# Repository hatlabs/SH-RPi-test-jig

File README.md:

# SH-RPi Test Jig software

This repository contains two separate PlatformIO projects, one Raspberry Pi software project, and KiCad hardware design that can be used to implement [SH-RPi](hatlabs.github.io/sh-rpi/) test jig functionality.

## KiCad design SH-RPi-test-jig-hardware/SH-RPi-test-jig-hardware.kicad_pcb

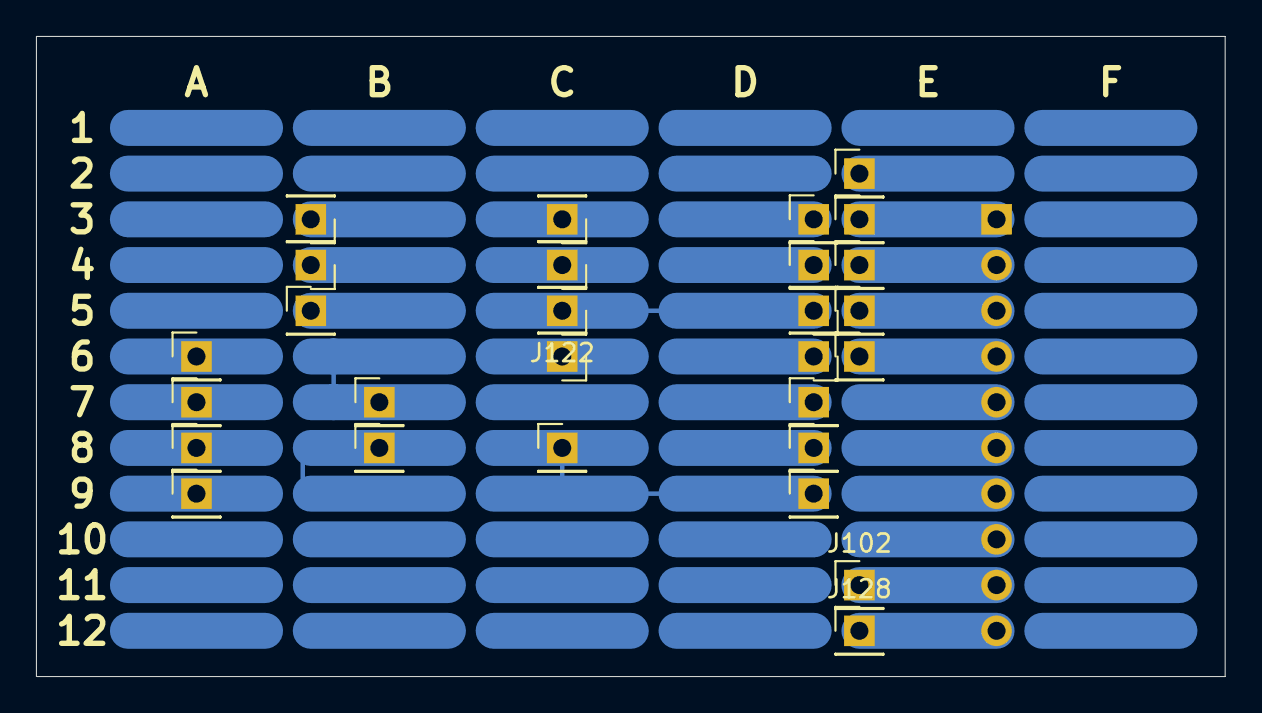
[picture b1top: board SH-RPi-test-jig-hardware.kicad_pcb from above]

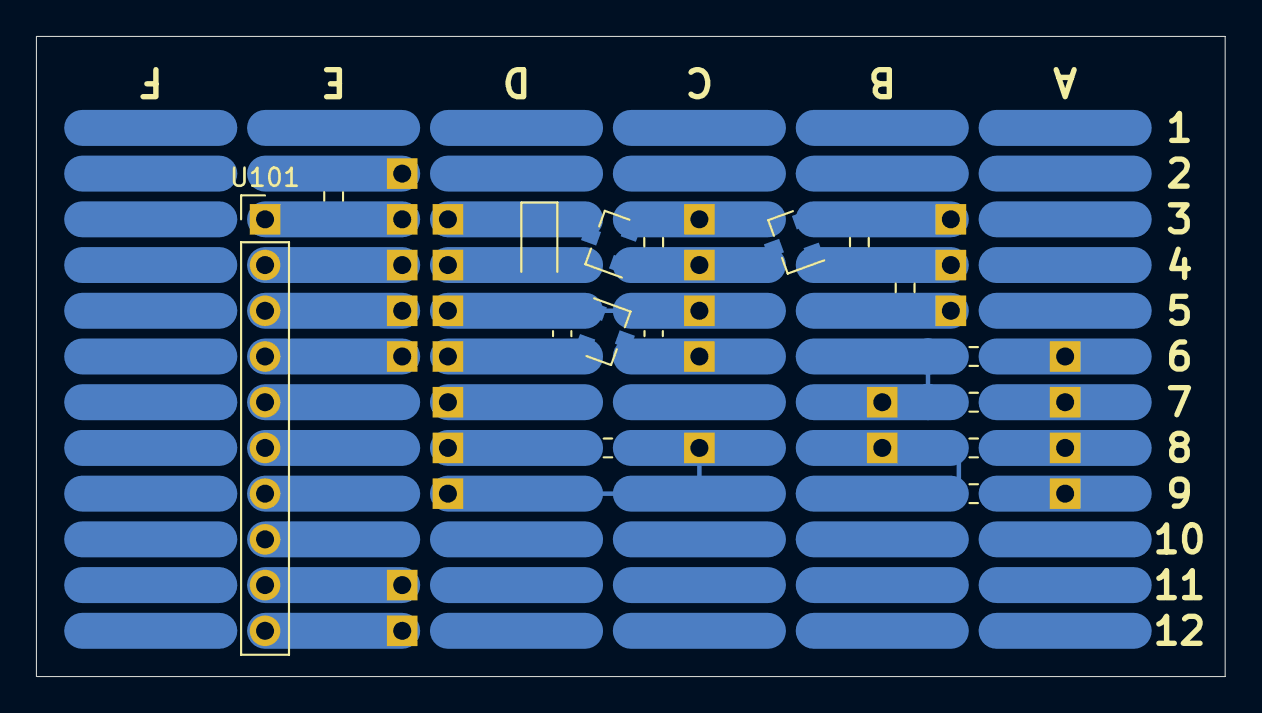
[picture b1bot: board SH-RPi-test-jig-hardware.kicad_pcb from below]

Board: 8 copper layers, 66.0 x 35.6 mm, 44 parts (16 on the bottom side), 17 nets.

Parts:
C101, C102: 2.2uF; C_0603_1608Metric
D101: SM4007PL; D_SOD-123F
J101, J102, J103, J104, J105, J106, J107, J108, J109, J110, J111, J112, J113, J114, J115, J116, J117, J118, J119, J120, J121, J122, J123, J124, J125, J126, J127, J128: Conn_01x01; PinHeader_1x01_P2.54mm_Vertical
Q101: S8050; SOT-23
Q102: DMP3098L; SOT-23
R101, R103: 10k; R_0603_1608Metric
R102, R104, R105, R106, R108, R109: 1k; R_0603_1608Metric
R107: 4k; R_0603_1608Metric
U101: ADS1115-module; PinHeader_1x10_P2.54mm_Vertical
U102: H7533; SOT-23

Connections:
+3V3: J114.1, R101.1, U101.1
+12V: J107.1, Q102.2, R104.1
/A2: J102.1, J110.1, R105.2, R106.1, U101.9
/A3: J112.1, J128.1, R107.2, R108.1, U101.10
/CONTROLLER_GPIO14: J103.1, R102.2
/CONTROLLER_GPIO15: J101.1, R101.2
/CONTROLLER_SCL: J116.1, U101.3
/CONTROLLER_SDA: J115.1, U101.4
/DUT_3V3: C102.1, J121.1, U102.2
/DUT_5V: C101.1, J109.1, J113.1, R105.1, U102.3
/DUT_12V: J111.1, R107.1
/DUT_POWER: D101.1, J108.1, Q102.3
/FLASHER_GPIO14: J118.1, R109.1
/FLASHER_GPIO15: J117.1, J119.1, R109.2
GND: C101.2, C102.2, D101.2, J106.1, J120.1, J122.1, J123.1, J124.1, J125.1, J126.1, J127.1, Q101.2, R103.2, R106.2, R108.2, U101.2, U102.1
unnamed: J104.1, Q101.1, R102.1, R103.1
unnamed: J105.1, Q101.3, Q102.1, R104.2

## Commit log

2021-05-06 initial import
2021-05-07 Partial controller implementation
2021-05-07 Hardware updates
2021-05-11 Partial responder implementation
2021-05-11 Controller WIP
2021-05-11 Responder gitignore
2021-05-12 Fully functional
